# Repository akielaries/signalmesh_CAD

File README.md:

# signalmesh CAD files
- KICAD schematic and PCB files
- renders of the schematics, PCB layers, and 3D view
- freeCAD render of the integrated signalmesh synthesizer

## layout

```
boards/<BOARD>/<vN_rM>/    one kicad project per version/revision
boards/_archive/           pre-split signalmesh v1-v4 dumps, not maintained
sim/                       spice + signal-integrity sim toolkit
tools/                     render, gallery, and fmc parity scripts
3d_assembly/               freeCAD assembly
```

boards today: 7SDD, ACM, AFFM, APM, AUDIO_BOARD, COMPUTE_BOARD, OSC_CTRL.

only the newest revision of each active board is rendered in ci. the allowlist
lives in `tools/render.sh` (`RENDER_BOARDS`) and doubles as the github actions
render matrix, so adding a board or bumping a revision is a one-line change.

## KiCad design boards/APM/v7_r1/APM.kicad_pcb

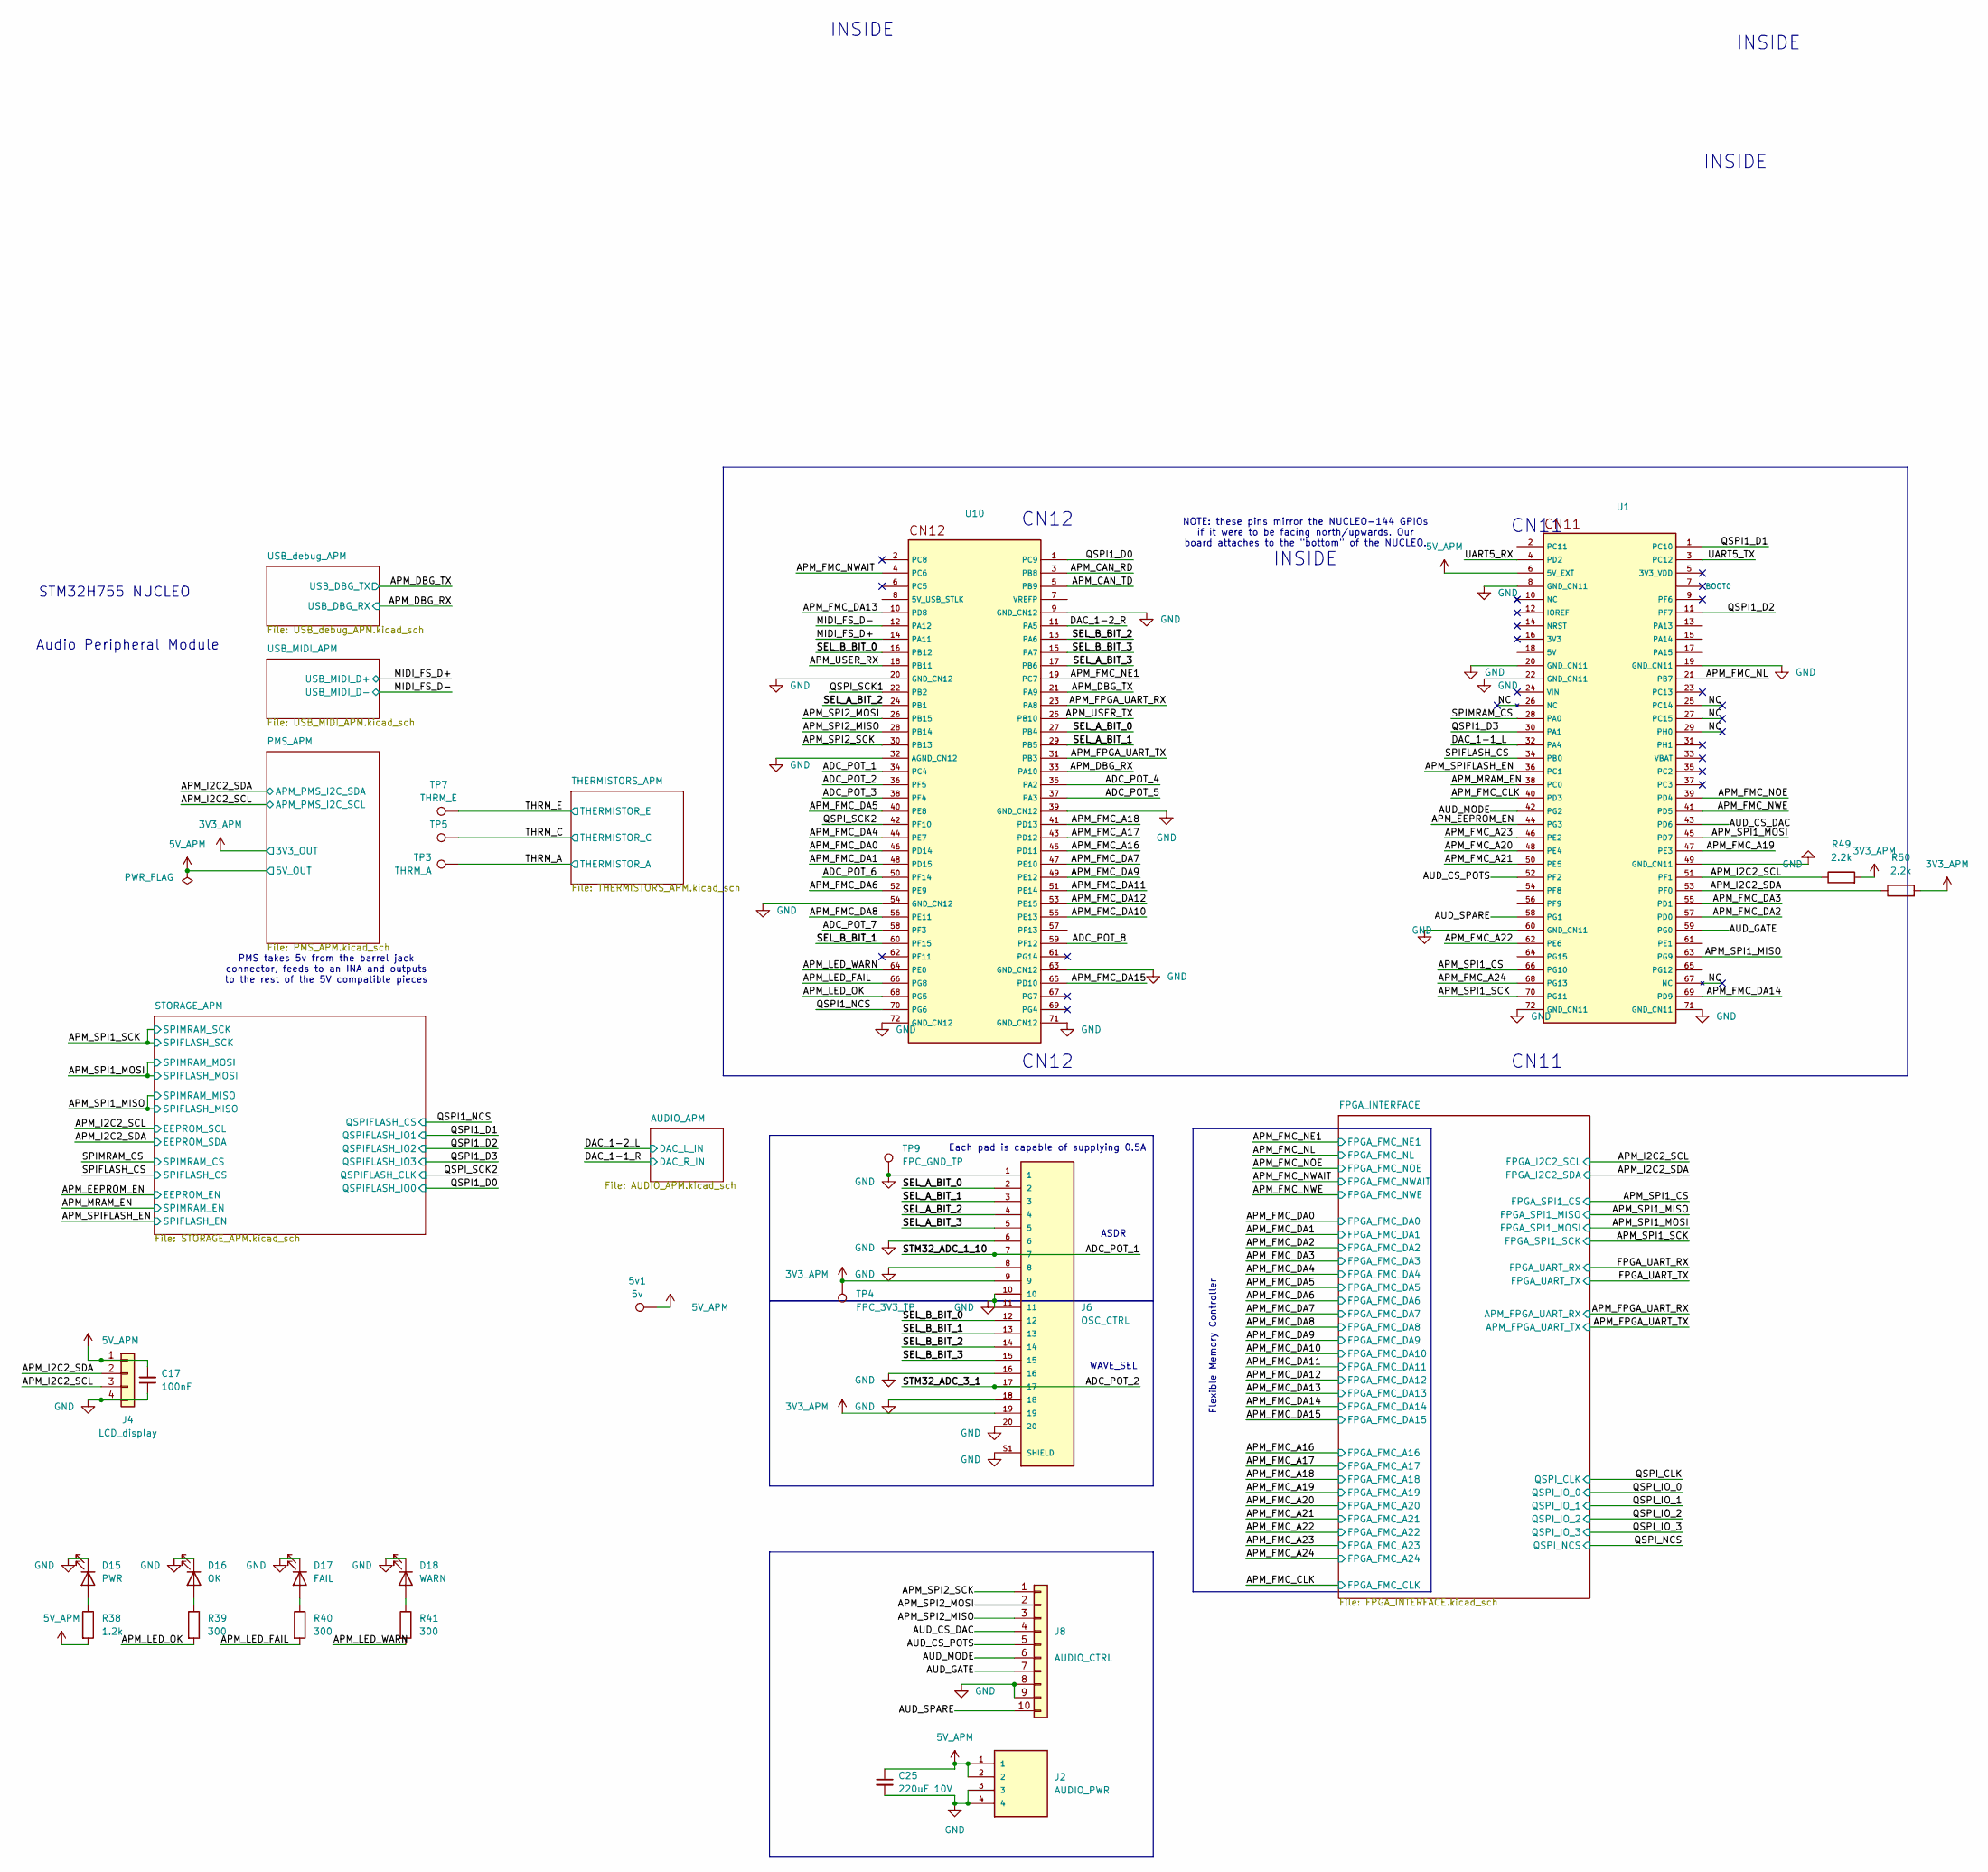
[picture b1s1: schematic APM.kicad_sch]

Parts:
5v1: 5v; TestPoint_Pad_D1.0mm
C17: 100nF; C_0805_2012Metric
C25: 220uF 10V; CP_Elec_4x3
D15: PWR; LED_0603_1608Metric
D16: OK; LED_0603_1608Metric
D17: FAIL; LED_0603_1608Metric
D18: WARN; LED_0603_1608Metric
J2: AUDIO_PWR; AMPHENOL_F3311A7H121004E200
J4: LCD_display; PinHeader_1x04_P2.54mm_Vertical_SMD_Pin1Left
J6: OSC_CTRL; GCT_FFC2B28-20-G; PARTREV A
J8: AUDIO_CTRL; Hirose_FH12-10S-0.5SH_1x10-1MP_P0.50mm_Horizontal
R38: 1.2k; R_0201_0603Metric; DigiKey_Part_Number 311-10.0KCRCT-ND
R39, R40, R41: 300; R_0201_0603Metric; DigiKey_Part_Number 311-10.0KCRCT-ND
R49, R50: 2.2k; R_0201_0603Metric; DigiKey_Part_Number 311-10.0KCRCT-ND
TP3: THRM_A; TestPoint_Pad_D1.0mm
TP4: FPC_3V3_TP; TestPoint_Pad_D1.0mm
TP5: THRM_C; TestPoint_Pad_D1.0mm
TP7: THRM_E; TestPoint_Pad_D1.0mm
TP9: FPC_GND_TP; TestPoint_Pad_D1.0mm
U1, U10: PinSocket_2x36_P2.54mm_Vertical

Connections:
3V3_APM: J6.9, J6.19, R49.2, R50.2, TP4.1 (1_1); also elsewhere on the board
5V_APM: 5v1.1 (1_1), C17.2, C25.1, J2.1, J2.2, J4.1, R38.2, U1.6 (5V_EXT); also elsewhere on the board
/ADC_POT_1: J6.7, U10.34 (PC4)
/ADC_POT_2: J6.17, U10.36 (PF5)
/ADC_POT_3: U10.38 (PF4)
/ADC_POT_4: U10.35 (PA2)
/ADC_POT_5: U10.37 (PA3)
/ADC_POT_6: U10.50 (PF14)
/ADC_POT_7: U10.58 (PF3)
/ADC_POT_8: U10.59 (PF12)
/APM_CAN_RD: U10.3 (PB8)
/APM_CAN_TD: U10.5 (PB9)
/APM_DBG_RX: U10.33 (PA10); also elsewhere on the board
/APM_DBG_TX: U10.21 (PA9); also elsewhere on the board
/APM_EEPROM_EN: U1.44 (PG3); also elsewhere on the board
/APM_FMC_A16: U10.45 (PD11); also elsewhere on the board
/APM_FMC_A17: U10.43 (PD12); also elsewhere on the board
/APM_FMC_A18: U10.41 (PD13); also elsewhere on the board
/APM_FMC_A19: U1.47 (PE3); also elsewhere on the board
/APM_FMC_A20: U1.48 (PE4); also elsewhere on the board
/APM_FMC_A21: U1.50 (PE5); also elsewhere on the board
/APM_FMC_A22: U1.62 (PE6); also elsewhere on the board
/APM_FMC_A23: U1.46 (PE2); also elsewhere on the board
/APM_FMC_A24: U1.68 (PG13); also elsewhere on the board
/APM_FMC_CLK: U1.40 (PD3); also elsewhere on the board
/APM_FMC_DA0: U10.46 (PD14); also elsewhere on the board
/APM_FMC_DA1: U10.48 (PD15); also elsewhere on the board
/APM_FMC_DA2: U1.57 (PD0); also elsewhere on the board
/APM_FMC_DA3: U1.55 (PD1); also elsewhere on the board
/APM_FMC_DA4: U10.44 (PE7); also elsewhere on the board
/APM_FMC_DA5: U10.40 (PE8); also elsewhere on the board
/APM_FMC_DA6: U10.52 (PE9); also elsewhere on the board
/APM_FMC_DA7: U10.47 (PE10); also elsewhere on the board
/APM_FMC_DA8: U10.56 (PE11); also elsewhere on the board
/APM_FMC_DA9: U10.49 (PE12); also elsewhere on the board
/APM_FMC_DA10: U10.55 (PE13); also elsewhere on the board
/APM_FMC_DA11: U10.51 (PE14); also elsewhere on the board
/APM_FMC_DA12: U10.53 (PE15); also elsewhere on the board
/APM_FMC_DA13: U10.10 (PD8); also elsewhere on the board
/APM_FMC_DA14: U1.69 (PD9); also elsewhere on the board
/APM_FMC_DA15: U10.65 (PD10); also elsewhere on the board
/APM_FMC_NE1: U10.19 (PC7); also elsewhere on the board
/APM_FMC_NL: U1.21 (PB7); also elsewhere on the board
/APM_FMC_NOE: U1.39 (PD4); also elsewhere on the board
/APM_FMC_NWAIT: U10.4 (PC6); also elsewhere on the board
/APM_FMC_NWE: U1.41 (PD5); also elsewhere on the board
/APM_FPGA_UART_RX: U10.23 (PA8); also elsewhere on the board
/APM_FPGA_UART_TX: U10.31 (PB3); also elsewhere on the board
/APM_I2C2_SCL: J4.3, R49.1, U1.51 (PF1); also elsewhere on the board
/APM_I2C2_SDA: J4.2, R50.1, U1.53 (PF0); also elsewhere on the board
/APM_LED_FAIL: R40.2, U10.66 (PG8)
/APM_LED_OK: R39.2, U10.68 (PG5)
/APM_LED_WARN: R41.2, U10.64 (PE0)
/APM_MRAM_EN: U1.38 (PC0); also elsewhere on the board
/APM_SPI1_CS: U1.66 (PG10); also elsewhere on the board
/APM_SPI1_MISO: U1.63 (PG9); also elsewhere on the board
/APM_SPI1_MOSI: U1.45 (PD7); also elsewhere on the board
/APM_SPI1_SCK: U1.70 (PG11); also elsewhere on the board
/APM_SPI2_MISO: J8.3, U10.28 (PB14)
/APM_SPI2_MOSI: J8.2, U10.26 (PB15)
/APM_SPI2_SCK: J8.1, U10.30 (PB13)
/APM_SPIFLASH_EN: U1.36 (PC1); also elsewhere on the board
/APM_USER_RX: U10.18 (PB11)
/APM_USER_TX: U10.25 (PB10)
/AUD_CS_DAC: J8.4, U1.43 (PD6)
/AUD_CS_POTS: J8.5, U1.52 (PF2)
/AUD_GATE: J8.7, U1.59 (PG0)
/AUD_MODE: J8.6, U1.42 (PG2)
/AUD_SPARE: J8.10, U1.58 (PG1)
/DAC_1-1_L: U1.32 (PA4)
/DAC_1-2_R: U10.11 (PA5)
/MIDI_FS_D+: U10.14 (PA11); also elsewhere on the board
/MIDI_FS_D-: U10.12 (PA12); also elsewhere on the board
/NC: U1.25 (PC14), U1.26 (NC), U1.27 (PC15), U1.29 (PH0), U1.67 (NC)
/QSPI1_D0: U10.1 (PC9); also elsewhere on the board
/QSPI1_D1: U1.1 (PC10); also elsewhere on the board
/QSPI1_D2: U1.11 (PF7); also elsewhere on the board
/QSPI1_D3: U1.30 (PA1); also elsewhere on the board
/QSPI1_NCS: U10.70 (PG6); also elsewhere on the board
/QSPI_SCK1: U10.22 (PB2)
/QSPI_SCK2: U10.42 (PF10); also elsewhere on the board
/SEL_A_BIT_0: J6.2, U10.27 (PB4)
/SEL_A_BIT_1: J6.3, U10.29 (PB5)
/SEL_A_BIT_2: J6.4, U10.24 (PB1)
/SEL_A_BIT_3: J6.5, U10.17 (PB6)
/SEL_B_BIT_0: J6.12, U10.16 (PB12)
/SEL_B_BIT_1: J6.13, U10.60 (PF15)
/SEL_B_BIT_2: J6.14, U10.13 (PA6)
/SEL_B_BIT_3: J6.15, U10.15 (PA7)
/SPIFLASH_CS: U1.34 (PB0); also elsewhere on the board
/SPIMRAM_CS: U1.28 (PA0); also elsewhere on the board
/THRM_A: TP3.1 (1_1); also elsewhere on the board
/THRM_C: TP5.1 (1_1); also elsewhere on the board
/THRM_E: TP7.1 (1_1); also elsewhere on the board
/UART5_RX: U1.4 (PD2)
/UART5_TX: U1.3 (PC12)
GND: C17.1, C25.2, D15.1 (K), D16.1 (K), D17.1 (K), D18.1 (K), J2.3, J2.4, J4.4, J6.1, J6.6, J6.8, J6.10, J6.11, J6.16, J6.18, J6.20, J6.S1 (SHIELD), J6.S2 (SHIELD), J8.8, J8.9, TP9.1 (1_1), U1.8 (GND_CN11), U1.19 (GND_CN11), U1.20 (GND_CN11), U1.22 (GND_CN11), U1.49 (GND_CN11), U1.60 (GND_CN11), U1.71 (GND_CN11), U1.72 (GND_CN11), U10.9 (GND_CN12), U10.20 (GND_CN12), U10.32 (AGND_CN12), U10.39 (GND_CN12), U10.54 (GND_CN12), U10.63 (GND_CN12), U10.71 (GND_CN12), U10.72 (GND_CN12); also elsewhere on the board
unnamed: D15.2 (A), R38.1
unnamed: D16.2 (A), R39.1
unnamed: D17.2 (A), R40.1
unnamed: D18.2 (A), R41.1

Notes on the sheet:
WAVE_SEL
STM32H755 NUCLEO
CN12
PMS takes 5v from the barrel jack connector, feeds to an INA and outputs to the rest of the 5V compatible pieces
INSIDE
Flexible Memory Controller
Audio Peripheral Module
NOTE: these pins mirror the NUCLEO-144 GPIOs if it were to be facing north/upwards. Our board attaches to the "bottom" of the NUCLEO.
Each pad is capable of supplying 0.5A
ASDR
CN11

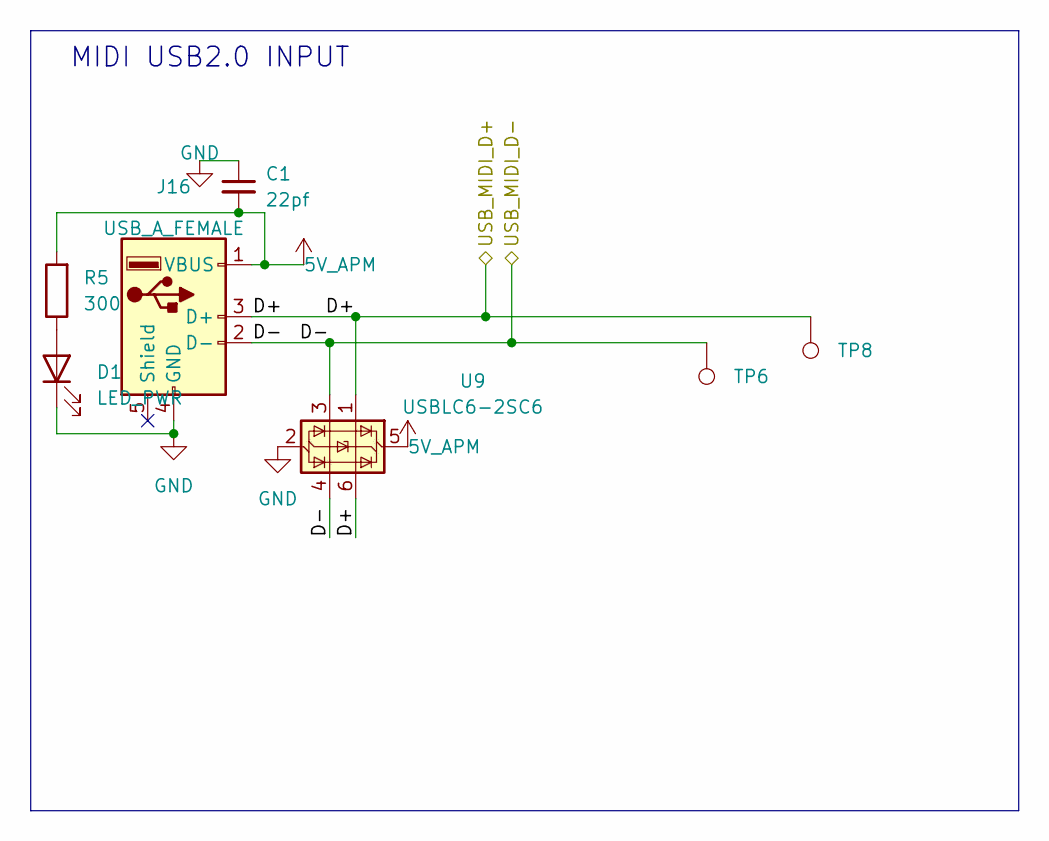
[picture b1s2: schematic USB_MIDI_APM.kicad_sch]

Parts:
C1: 22pf; C_0805_2012Metric
D1: LED_PWR; LED_0603_1608Metric
J16: USB_A_FEMALE; USB_A_Molex_67643_Horizontal
R5: 300; R_0201_0603Metric; DigiKey_Part_Number 311-10.0KCRCT-ND
TP6: MIDI_D-; TestPoint_Pad_D1.0mm
TP8: MIDI_D+; TestPoint_Pad_D1.0mm
U9: USBLC6-2SC6; SOT-23-6

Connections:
5V_APM: C1.2, J16.1 (VBUS), R5.2, U9.5 (VBUS); also elsewhere on the board
/MIDI_FS_D+: J16.3 (D+), TP8.1 (1_1), U9.1 (I/O1), U9.6 (I/O1); also elsewhere on the board
/MIDI_FS_D-: J16.2 (D-), TP6.1 (1_1), U9.3 (I/O2), U9.4 (I/O2); also elsewhere on the board
GND: C1.1, D1.1 (K), J16.4 (GND), U9.2 (GND); also elsewhere on the board
unnamed: D1.2 (A), R5.1

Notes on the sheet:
MIDI USB2.0 INPUT

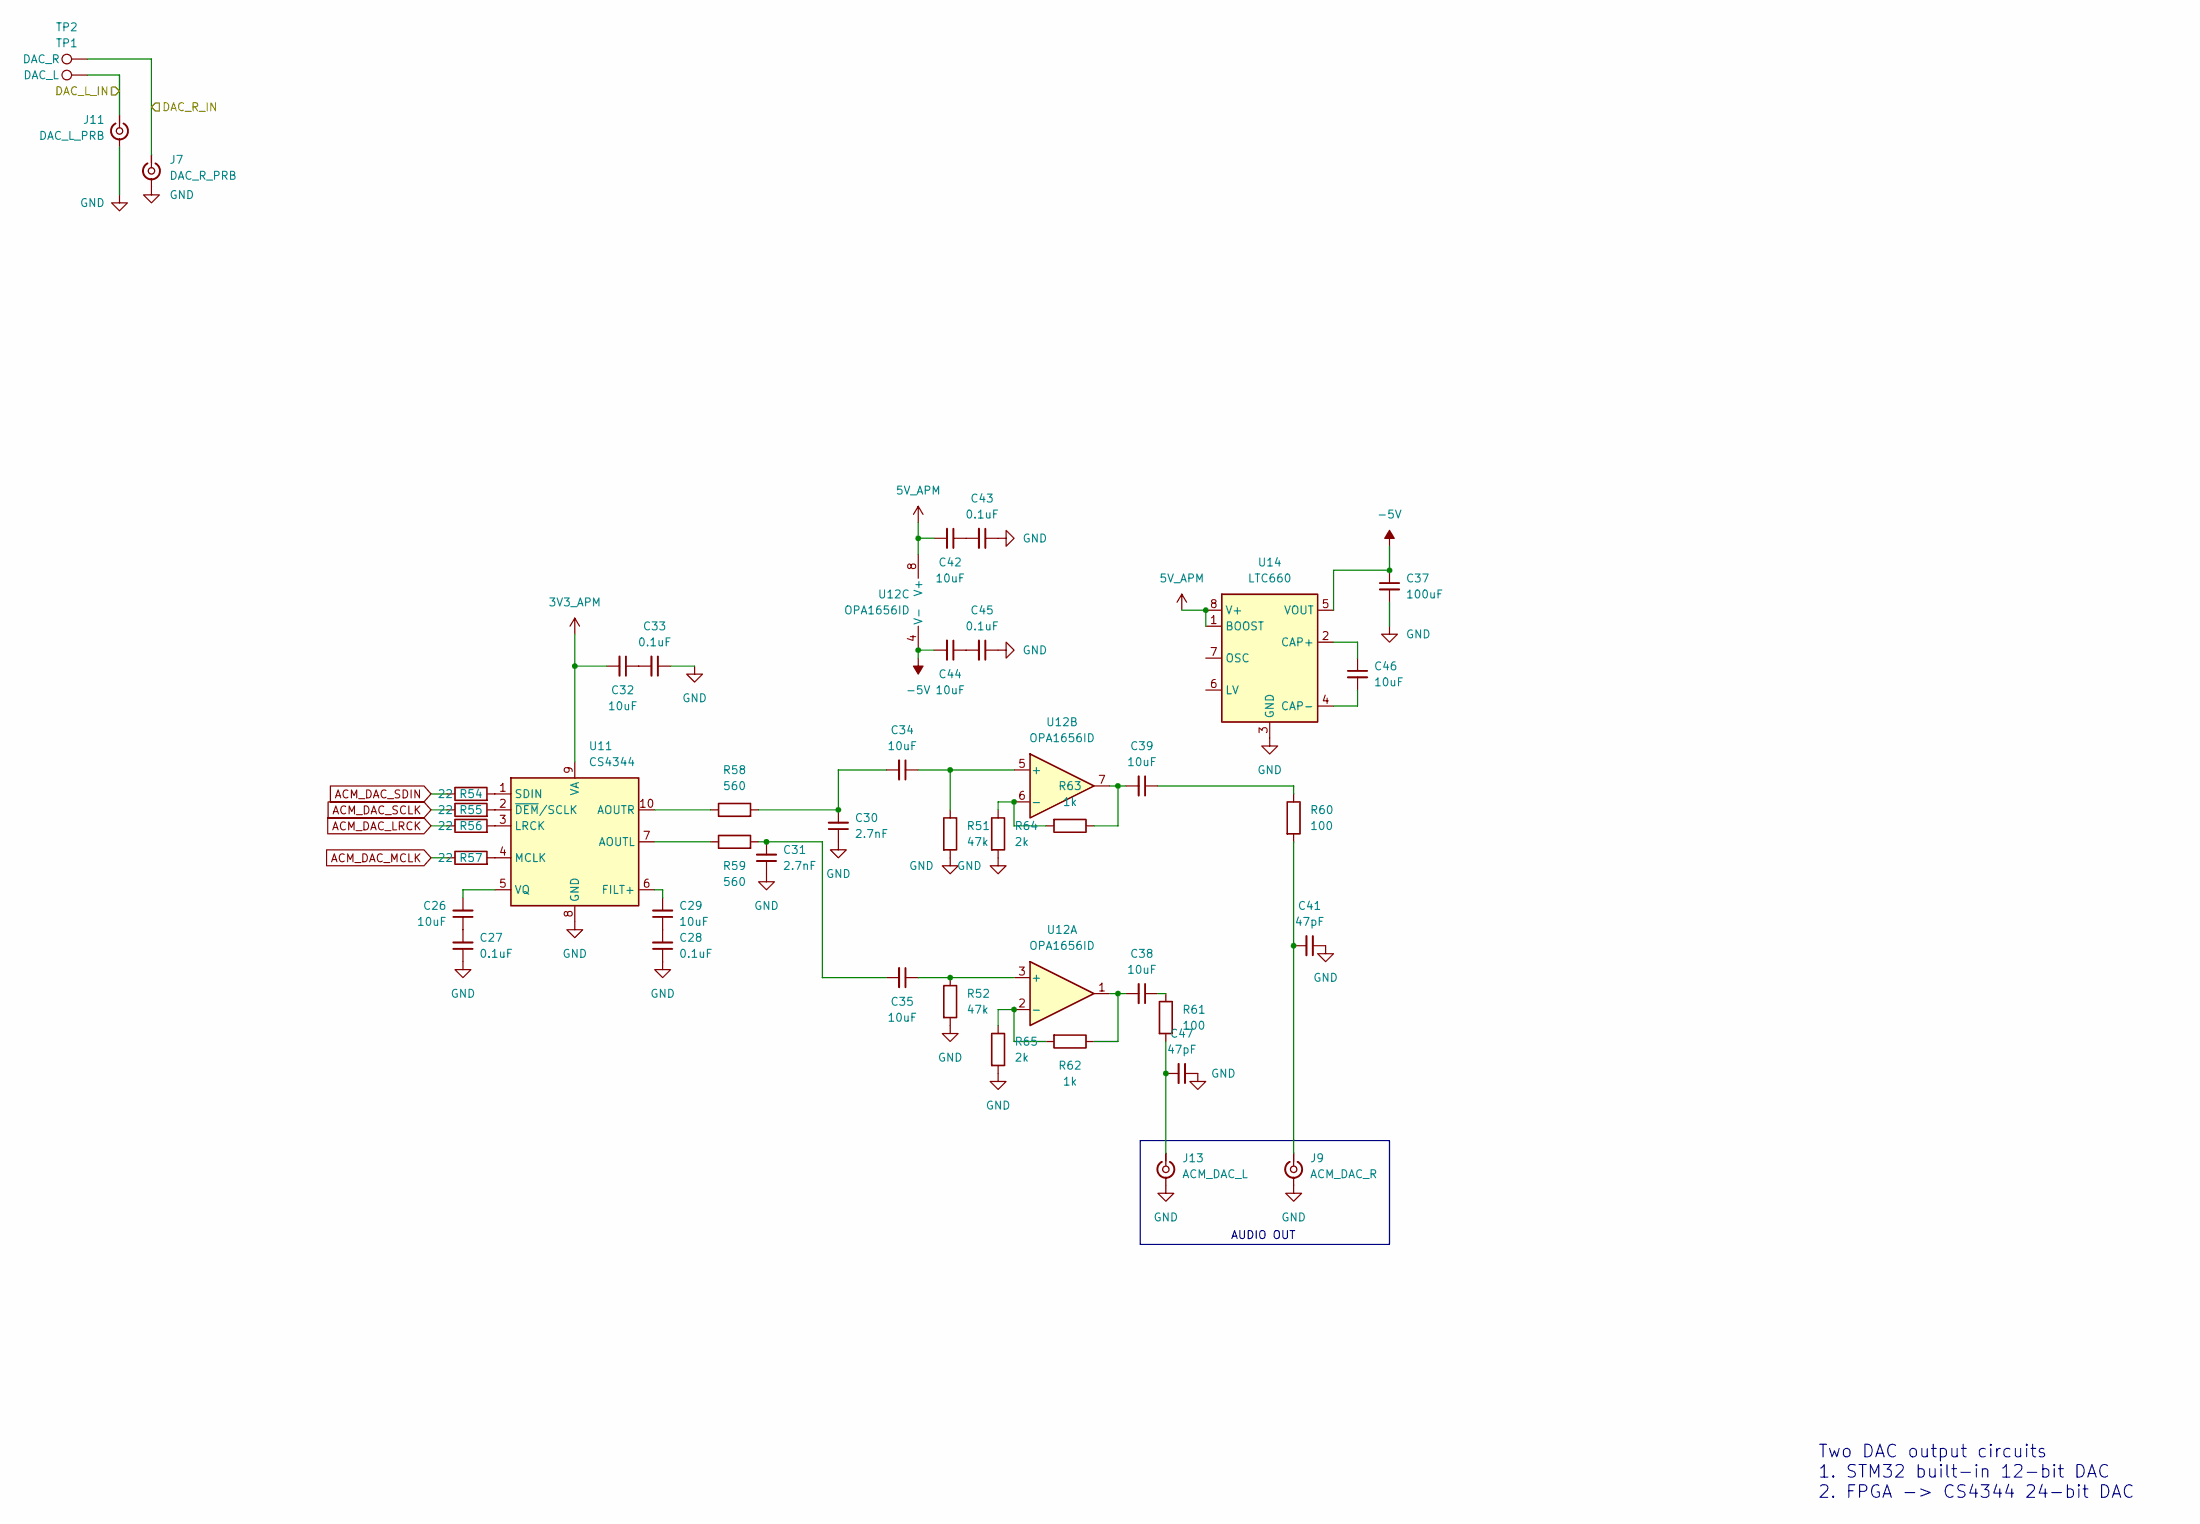
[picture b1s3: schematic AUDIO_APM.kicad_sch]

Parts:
C26, C29, C32, C34, C35, C38, C39, C42, C44, C46: 10uF; C_0805_2012Metric
C27, C28, C33, C43, C45: 0.1uF; C_0402_1005Metric
C30, C31: 2.7nF; C_0402_1005Metric
C37: 100uF; C_0805_2012Metric
C41, C47: 47pF; C_0402_1005Metric
J7: DAC_R_PRB; U.FL_Hirose_U.FL-R-SMT-1_Vertical
J9: ACM_DAC_R; U.FL_Hirose_U.FL-R-SMT-1_Vertical
J11: DAC_L_PRB; U.FL_Hirose_U.FL-R-SMT-1_Vertical
J13: ACM_DAC_L; U.FL_Hirose_U.FL-R-SMT-1_Vertical
R51, R52: 47k; R_0201_0603Metric; DigiKey_Part_Number 311-10.0KCRCT-ND
R54, R55, R56, R57: 22; R_0201_0603Metric; DigiKey_Part_Number 311-10.0KCRCT-ND
R58, R59: 560; R_0201_0603Metric; DigiKey_Part_Number 311-10.0KCRCT-ND
R60, R61: 100; R_0201_0603Metric; DigiKey_Part_Number 311-10.0KCRCT-ND
R62, R63: 1k; R_0201_0603Metric; DigiKey_Part_Number 311-10.0KCRCT-ND
R64, R65: 2k; R_0201_0603Metric; DigiKey_Part_Number 311-10.0KCRCT-ND
TP1: DAC_L; TestPoint_Pad_D1.0mm
TP2: DAC_R; TestPoint_Pad_D1.0mm
U11: CS4344; TSSOP-10_3x3mm_P0.5mm
U12: OPA1656ID; SOIC-8_3.9x4.9mm_P1.27mm
U14: LTC660; SOIC-8_3.9x4.9mm_P1.27mm

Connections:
3V3_APM: C32.2, U11.9 (VA); also elsewhere on the board
5V_APM: C42.2, U12.8 (V+), U14.1 (BOOST), U14.8 (V+); also elsewhere on the board
-5V: C37.1, C44.2, U12.4 (V-), U14.5 (VOUT)
/DAC_1-1_R: J7.1 (In), TP2.1 (1_1)
/DAC_1-2_L: J11.1 (In), TP1.1 (1_1)
ACM_DAC_LRCK: R56.1; also elsewhere on the board
ACM_DAC_MCLK: R57.1; also elsewhere on the board
ACM_DAC_SCLK: R55.1; also elsewhere on the board
ACM_DAC_SDIN: R54.1; also elsewhere on the board
GND: C27.1, C28.1, C30.1, C31.1, C33.1, C37.2, C41.1, C43.1, C45.1, C47.1, J7.2 (Ext), J9.2 (Ext), J11.2 (Ext), J13.2 (Ext), R51.2, R52.2, R64.2, R65.2, U11.8 (GND), U14.3 (GND); also elsewhere on the board
unnamed: C26.1, C27.2
unnamed: C28.2, C29.1
unnamed: C30.2, C34.2, R58.2
unnamed: C31.2, C35.2, R59.2
unnamed: C32.1, C33.2
unnamed: C38.1, R61.1
unnamed: C38.2, R62.1, U12.1
unnamed: C39.1, R60.1
unnamed: C39.2, R63.1, U12.7
unnamed: C42.1, C43.2
unnamed: C44.1, C45.2
unnamed: C41.2, J9.1 (In), R60.2
unnamed: C47.2, J13.1 (In), R61.2
unnamed: R59.1, U11.7 (AOUTL)
unnamed: R58.1, U11.10 (AOUTR)
unnamed: C29.2, U11.6 (FILT+)
unnamed: R56.2, U11.3 (LRCK)
unnamed: R57.2, U11.4 (MCLK)
unnamed: R54.2, U11.1 (SDIN)
unnamed: C26.2, U11.5 (VQ)
unnamed: R55.2, U11.2 (~DEM/SCLK)
unnamed: C35.1, R52.1, U12.3 (+)
unnamed: R62.2, R65.1, U12.2 (-)
unnamed: C34.1, R51.1, U12.5 (+)
unnamed: R63.2, R64.1, U12.6 (-)
unnamed: C46.1, U14.2 (CAP+)
unnamed: C46.2, U14.4 (CAP-)

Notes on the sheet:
AUDIO OUT
Two DAC output circuits 1. STM32 built-in 12-bit DAC 2. FPGA -> CS4344 24-bit DAC

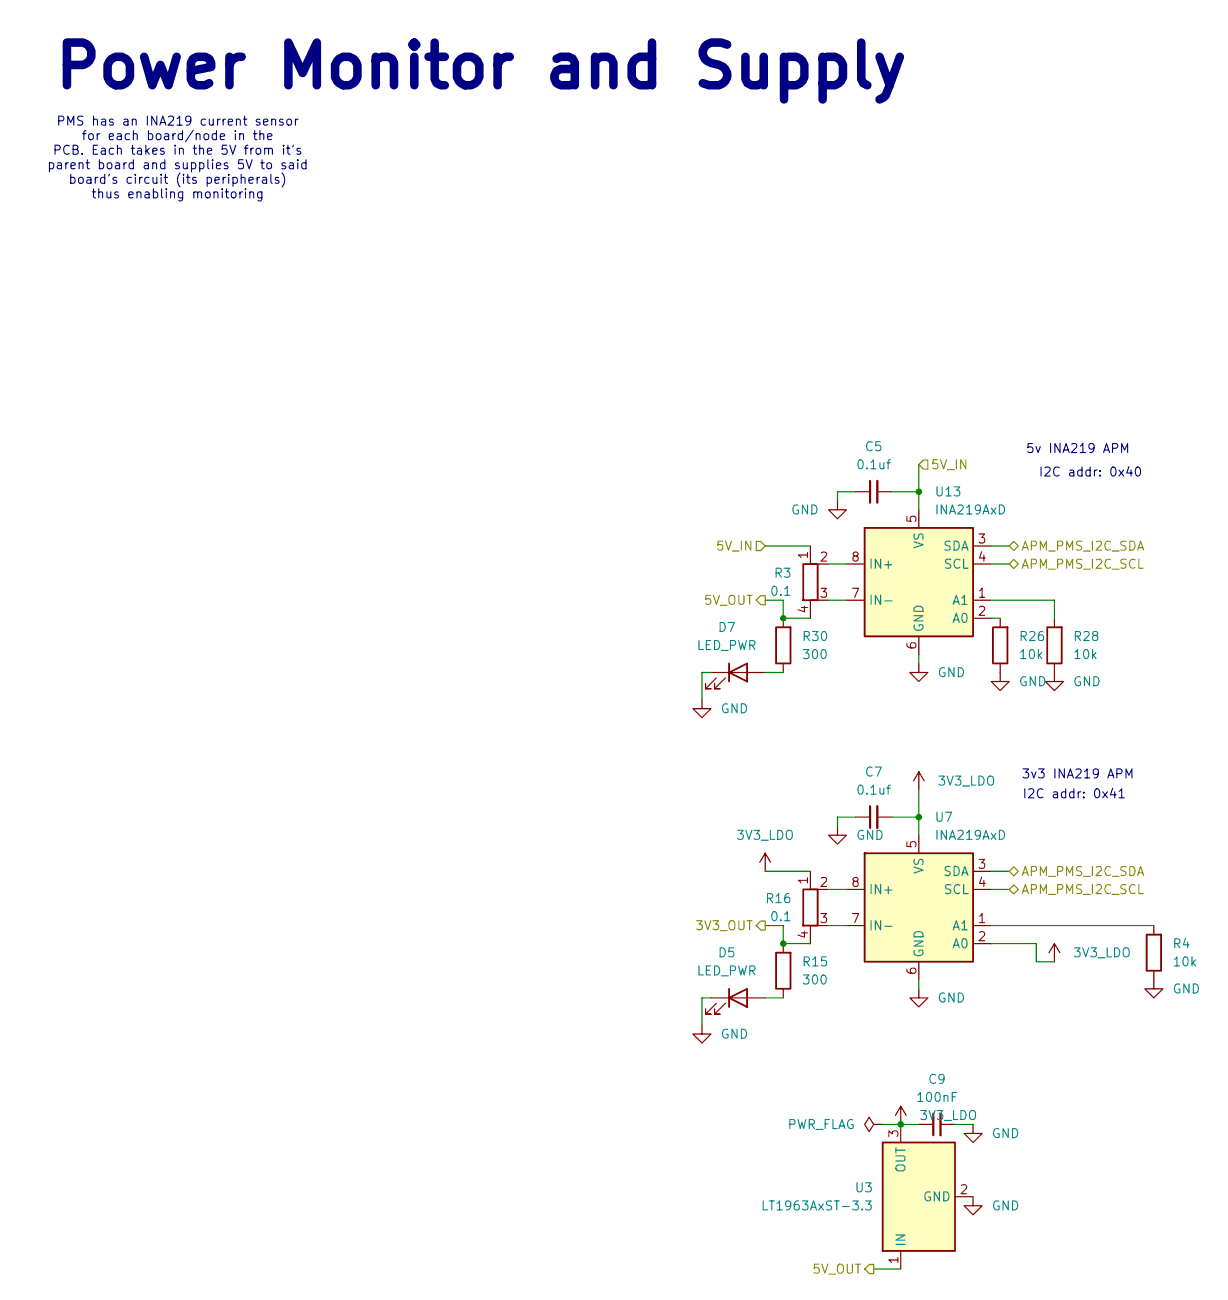
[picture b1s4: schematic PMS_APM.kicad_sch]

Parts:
C5, C7: 0.1uf; C_0805_2012Metric
C9: 100nF; C_0805_2012Metric
D5, D7: LED_PWR; LED_0603_1608Metric
R3, R16: 0.1; R_Shunt_Ohmite_LVK12
R4, R26, R28: 10k; R_0201_0603Metric; DigiKey_Part_Number 311-10.0KCRCT-ND
R15, R30: 300; R_0201_0603Metric; DigiKey_Part_Number 311-10.0KCRCT-ND
U3: LT1963AxST-3.3; SOT-223-3_TabPin2
U7, U13: INA219AxD; SOIC-8_3.9x4.9mm_P1.27mm

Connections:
3V3_APM: R15.2, R16.4; also elsewhere on the board
5V_APM: R3.4, R30.2, U3.1 (IN); also elsewhere on the board
/APM_I2C2_SCL: U7.4 (SCL), U13.4 (SCL); also elsewhere on the board
/APM_I2C2_SDA: U7.3 (SDA), U13.3 (SDA); also elsewhere on the board
GND: C5.1, C7.1, C9.2, D5.1 (K), D7.1 (K), R4.1, R26.1, R28.1, U3.2 (GND), U7.6 (GND), U13.6 (GND); also elsewhere on the board
unnamed: D5.2 (A), R15.1
unnamed: D7.2 (A), R30.1
unnamed: R4.2, U7.1 (A1)
unnamed: R16.2, U7.8 (IN+)
unnamed: R16.3, U7.7 (IN-)
unnamed: R26.2, U13.2 (A0)
unnamed: R28.2, U13.1 (A1)
unnamed: R3.2, U13.8 (IN+)
unnamed: R3.3, U13.7 (IN-)

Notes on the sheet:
I2C addr: 0x40
Power Monitor and Supply
3v3 INA219 APM
PMS has an INA219 current sensor for each board/node in the PCB. Each takes in the 5V from it's parent board and supplies 5V to said board's circuit (its peripherals) thus enabling monitoring
I2C addr: 0x41
5v INA219 APM

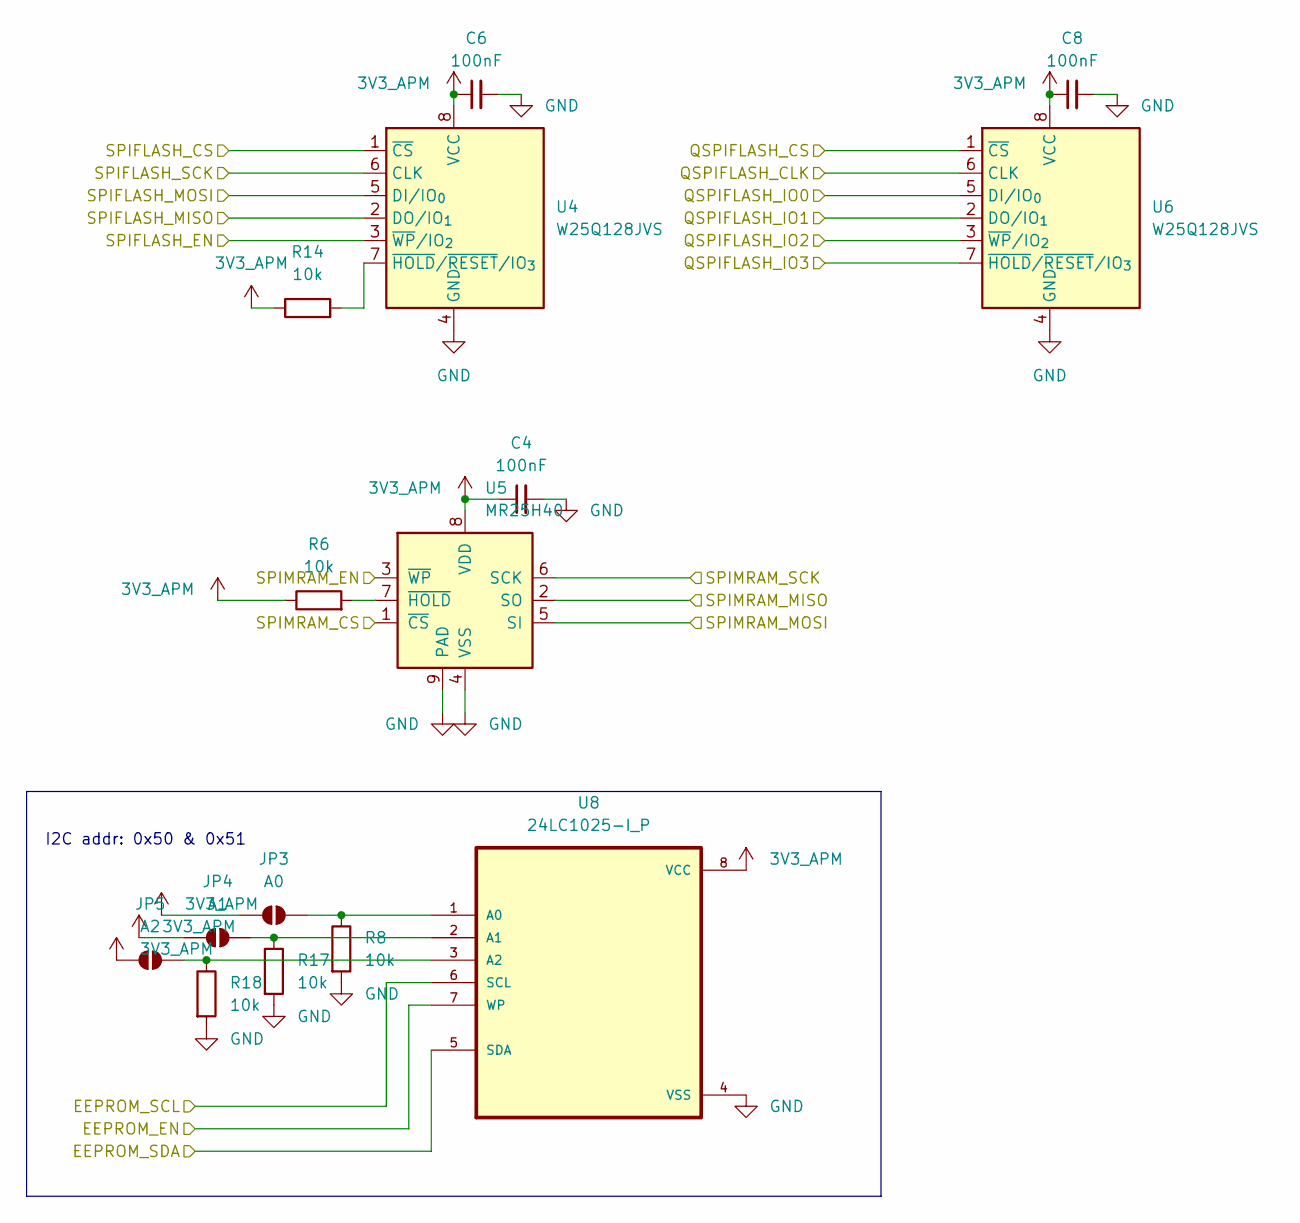
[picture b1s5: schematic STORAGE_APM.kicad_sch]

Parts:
C4, C6, C8: 100nF; C_0805_2012Metric
JP3: A0; SolderJumper-2_P1.3mm_Open_Pad1.0x1.5mm
JP4: A1; SolderJumper-2_P1.3mm_Open_Pad1.0x1.5mm
JP5: A2; SolderJumper-2_P1.3mm_Open_Pad1.0x1.5mm
R6, R8, R14, R17, R18: 10k; R_0201_0603Metric; DigiKey_Part_Number 311-10.0KCRCT-ND
U4, U6: W25Q128JVS; SOIC-8_5.3x5.3mm_P1.27mm
U5: MR25H40; DFN-S-8-1EP_6x5mm_P1.27mm
U8: 24LC1025-I_P; DIP787W46P254L927H533Q8

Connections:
3V3_APM: C4.1, C6.1, C8.1, JP3.2 (B), JP4.2 (B), JP5.2 (B), R6.1, R14.1, U4.8 (VCC), U5.8 (VDD), U6.8 (VCC), U8.8 (VCC); also elsewhere on the board
/APM_EEPROM_EN: U8.7 (WP); also elsewhere on the board
/APM_I2C2_SCL: U8.6 (SCL); also elsewhere on the board
/APM_I2C2_SDA: U8.5 (SDA); also elsewhere on the board
/APM_MRAM_EN: U5.3 (~WP); also elsewhere on the board
/APM_SPI1_MISO: U4.2 (DO/IO_{1}), U5.2 (SO); also elsewhere on the board
/APM_SPI1_MOSI: U4.5 (DI/IO_{0}), U5.5 (SI); also elsewhere on the board
/APM_SPI1_SCK: U4.6 (CLK), U5.6 (SCK); also elsewhere on the board
/APM_SPIFLASH_EN: U4.3 (~WP/IO_{2}); also elsewhere on the board
/QSPI1_D0: U6.5 (DI/IO_{0}); also elsewhere on the board
/QSPI1_D1: U6.2 (DO/IO_{1}); also elsewhere on the board
/QSPI1_D2: U6.3 (~WP/IO_{2}); also elsewhere on the board
/QSPI1_D3: U6.7 (~HOLD/~RESET/IO_{3}); also elsewhere on the board
/QSPI1_NCS: U6.1 (~CS); also elsewhere on the board
/QSPI_SCK2: U6.6 (CLK); also elsewhere on the board
/SPIFLASH_CS: U4.1 (~CS); also elsewhere on the board
/SPIMRAM_CS: U5.1 (~CS); also elsewhere on the board
GND: C4.2, C6.2, C8.2, R8.2, R17.2, R18.2, U4.4 (GND), U5.4 (VSS), U5.9 (PAD), U6.4 (GND), U8.4 (VSS); also elsewhere on the board
unnamed: JP3.1 (A), R8.1, U8.1 (A0)
unnamed: JP4.1 (A), R17.1, U8.2 (A1)
unnamed: JP5.1 (A), R18.1, U8.3 (A2)
unnamed: R14.2, U4.7 (~HOLD/~RESET/IO_{3})
unnamed: R6.2, U5.7 (~HOLD)

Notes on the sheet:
I2C addr: 0x50 & 0x51
